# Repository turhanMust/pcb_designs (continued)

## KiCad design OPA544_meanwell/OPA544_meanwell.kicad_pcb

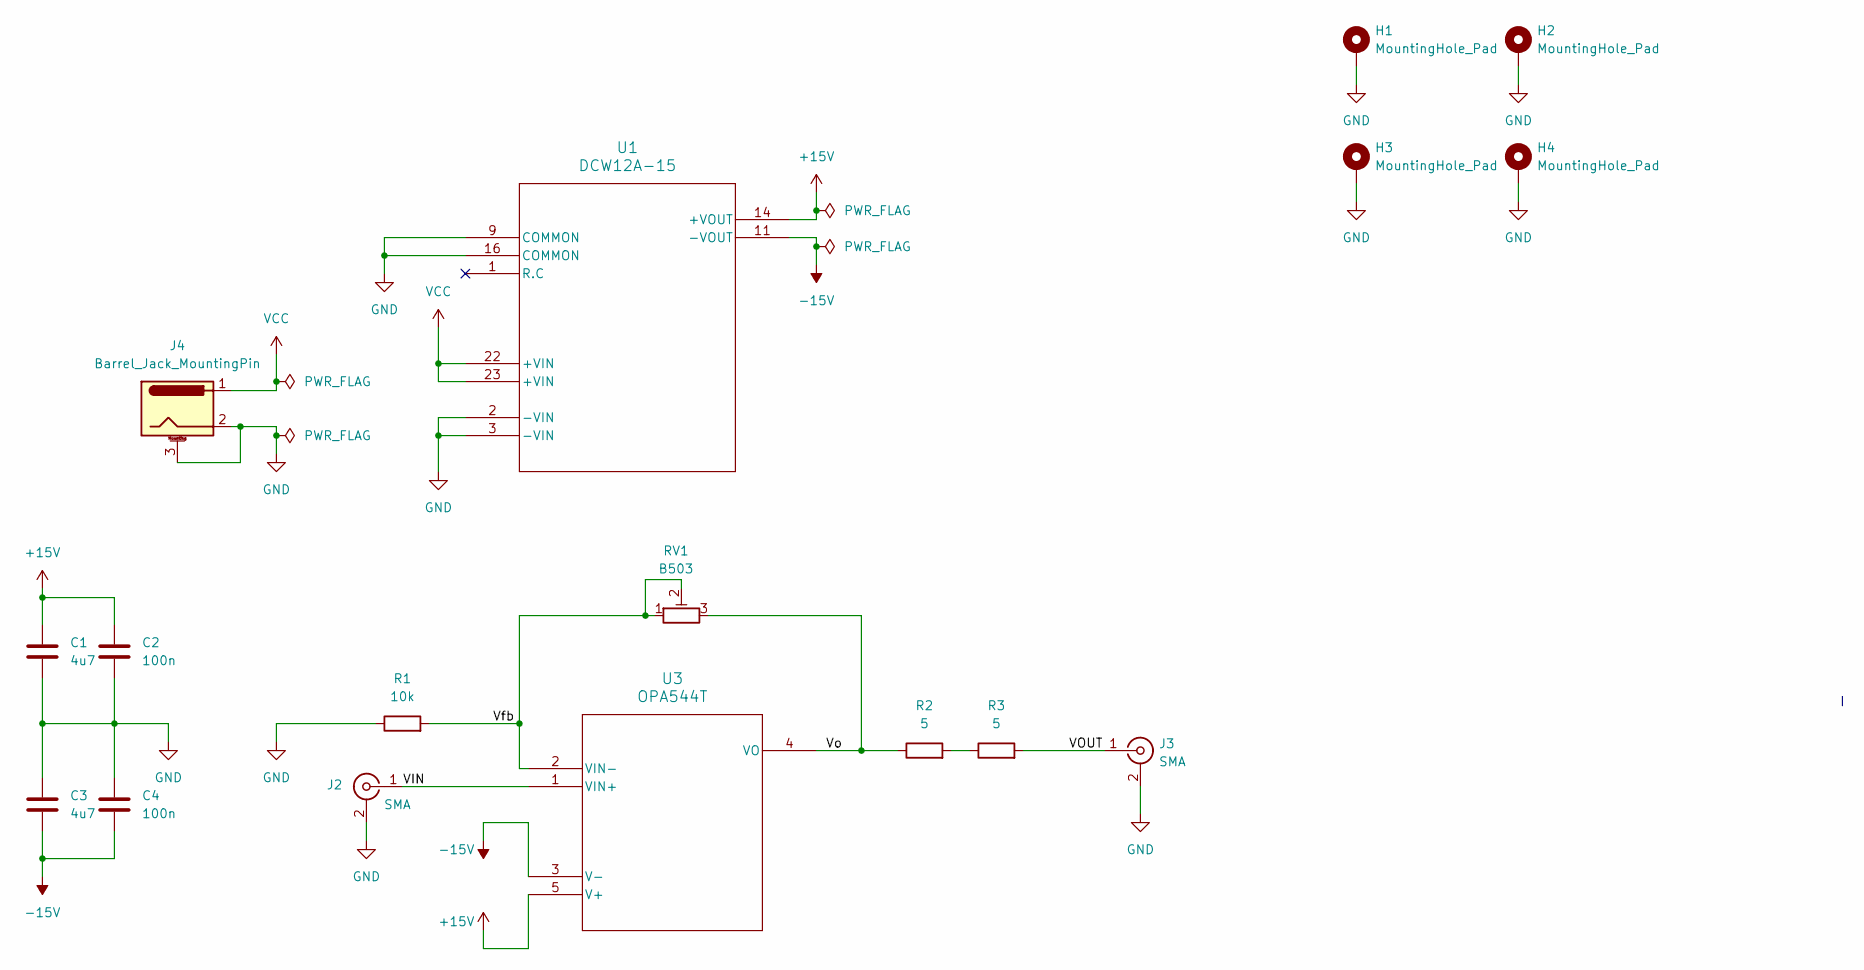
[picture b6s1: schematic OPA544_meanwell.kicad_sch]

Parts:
C1, C3: 4u7; C_0805_2012Metric
C2, C4: 100n; C_0603_1608Metric
H1, H2, H3, H4: MountingHole_Pad; MountingHole_2.5mm_Pad
J2, J3: SMA; SMA_Samtec_SMA-J-P-X-ST-EM1_EdgeMount
J4: Barrel_Jack_MountingPin; BarrelJack_Horizontal
R1: 10k; R_0603_1608Metric
R2, R3: 5; R_1210_3225Metric
RV1: B503; Potentiometer_Bourns_3296W_Vertical
U1: DCW12A-15; SCW12&slash_DCW12_MWU
U3: OPA544T; KC5

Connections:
+15V: C1.1, C2.1, U1.14 (+VOUT), U3.5 (V+)
-15V: C3.2, C4.2, U1.11 (-VOUT), U3.3 (V-)
/VIN: J2.1 (In), U3.1 (VIN+)
/VOUT: J3.1 (In), R3.2
/Vfb: R1.2, RV1.1, RV1.2, U3.2 (VIN-)
/Vo: R2.1, RV1.3, U3.4 (VO)
GND: C1.2, C2.2, C3.1, C4.1, H1.1, H2.1, H3.1, H4.1, J2.2 (Ext), J3.2 (Ext), J4.2, J4.3 (MountPin), R1.1, U1.2 (-VIN), U1.3 (-VIN), U1.9 (COMMON), U1.16 (COMMON)
unnamed: R2.2, R3.1
VCC: J4.1, U1.22 (+VIN), U1.23 (+VIN)

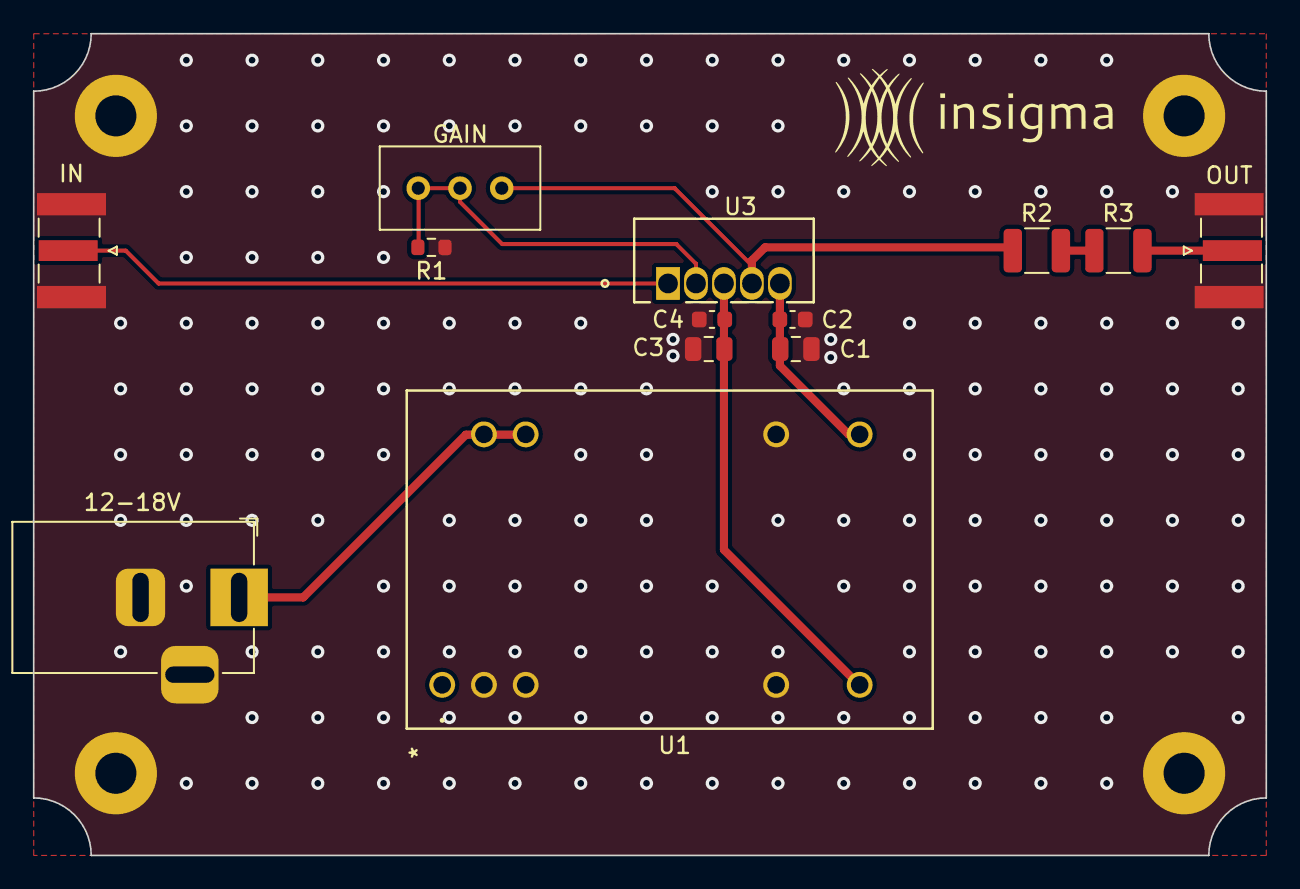
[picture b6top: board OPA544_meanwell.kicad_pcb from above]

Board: 2 copper layers, 75.0 x 50.0 mm, 17 parts (0 on the bottom side), 9 nets.

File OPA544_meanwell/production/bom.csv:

Designator,Footprint,Quantity,Value,LCSC Part #
"C1, C3",0805,2,4u7,
"C2, C4",0603,2,100n,
"J2, J3",SMA_Samtec_SMA-J-P-X-ST-EM1_EdgeMount,2,SMA,
J4,BarrelJack_Horizontal,1,Barrel_Jack_MountingPin,
R1,0603,1,10k,
"R2, R3",1210,2,5,
RV1,Potentiometer_Bourns_3296W_Vertical,1,B503,
U1,SCW12&slash_DCW12_MWU,1,DCW12A-15,
U3,KC5,1,OPA544T,

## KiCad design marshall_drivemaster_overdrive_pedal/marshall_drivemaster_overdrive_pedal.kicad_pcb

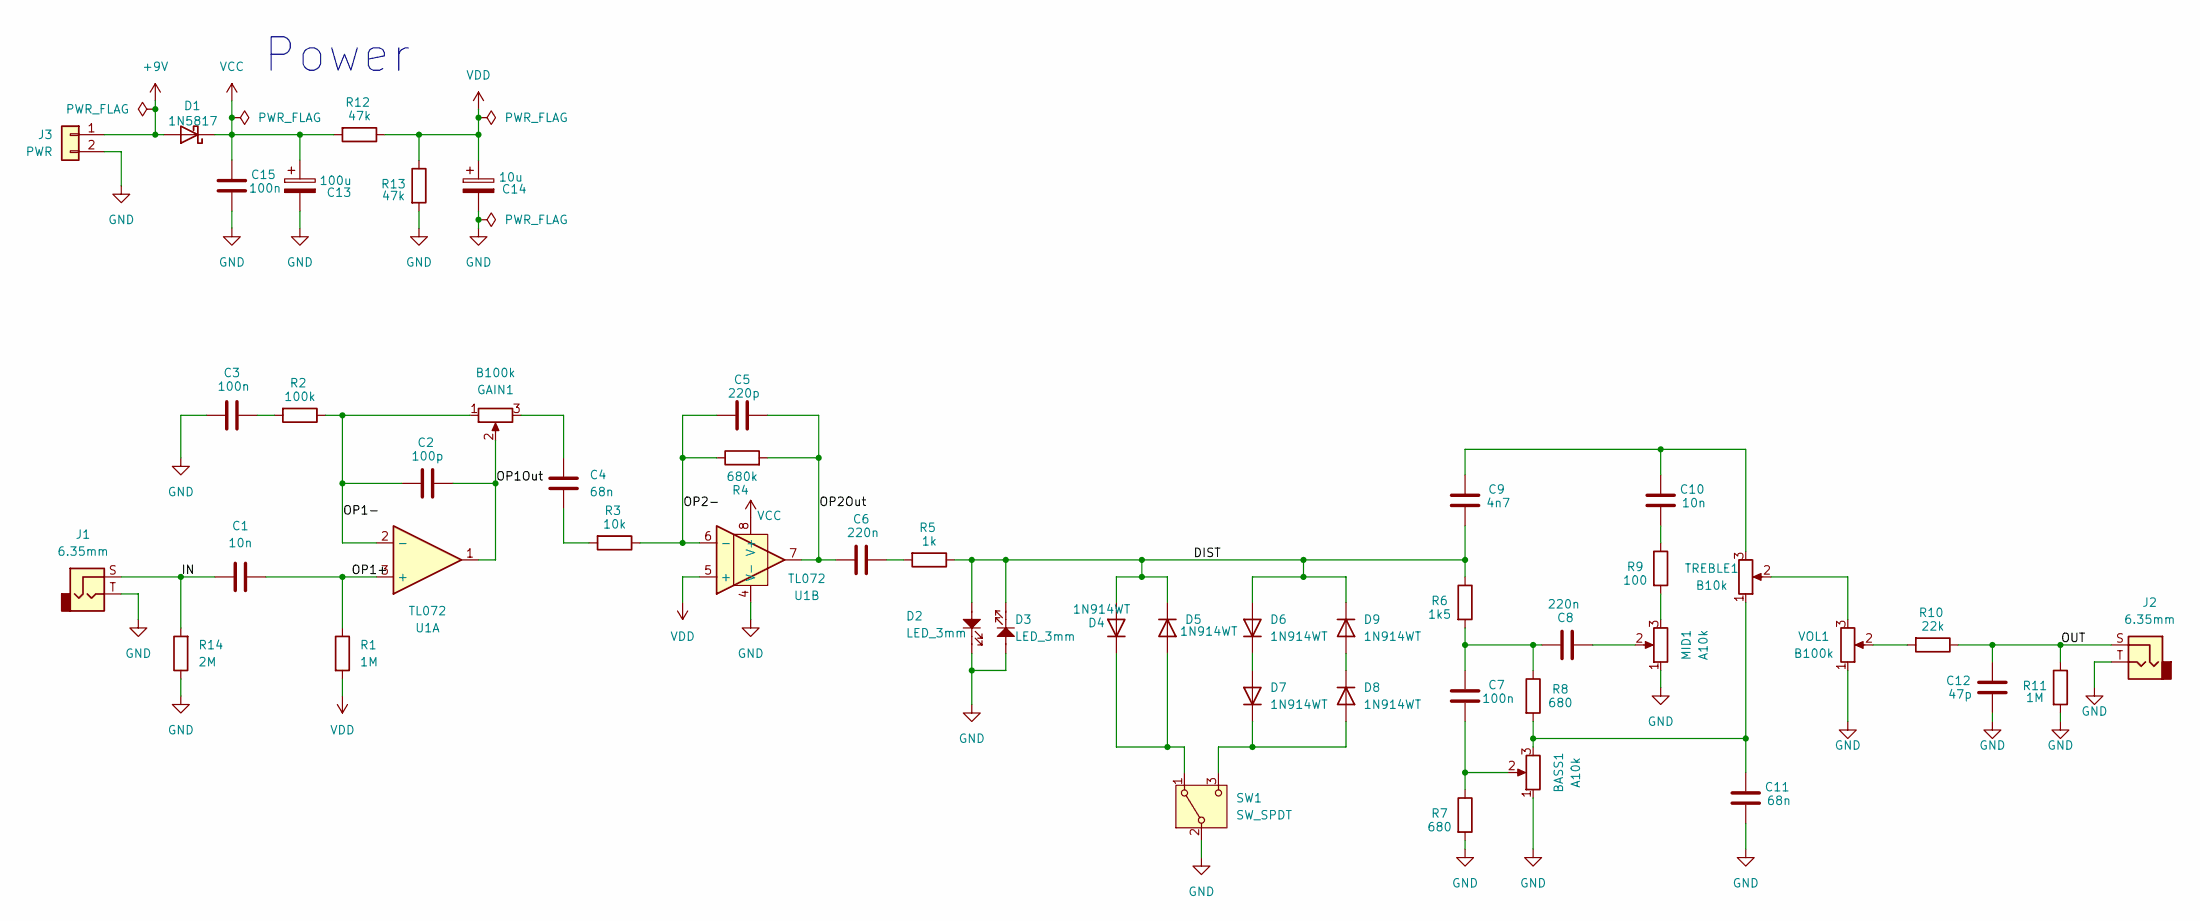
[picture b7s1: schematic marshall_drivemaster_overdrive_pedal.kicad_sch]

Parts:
BASS1: A10k; Potentiometer_Bourns_PTV09A-1_Single_Vertical
C1, C10: 10n; C_0603_1608Metric
C2: 100p; C_0603_1608Metric
C3, C7, C15: 100n; C_0603_1608Metric
C4, C11: 68n; C_0603_1608Metric
C5: 220p; C_0603_1608Metric
C6, C8: 220n; C_0603_1608Metric
C9: 4n7; C_0603_1608Metric
C12: 47p; C_0603_1608Metric
C13: 100u; CP_Radial_D5.0mm_P2.00mm
C14: 10u; CP_Radial_D5.0mm_P2.00mm
D1: 1N5817; D_DO-41_SOD81_P10.16mm_Horizontal
D2, D3: LED_3mm; LED_D3.0mm
D4, D5, D6, D7, D8, D9: 1N914WT; D_SOD-523
GAIN1: B100k; Potentiometer_Bourns_PTV09A-1_Single_Vertical
J1, J2: 6.35mm; Jack_6.35mm_Neutrik_NMJ4HCD2_Horizontal
J3: PWR; SolderWire-0.25sqmm_1x02_P4.2mm_D0.65mm_OD1.7mm
MID1: A10k; Potentiometer_Bourns_PTV09A-1_Single_Vertical
R1, R11: 1M; R_0603_1608Metric
R2: 100k; R_0603_1608Metric
R3: 10k; R_0603_1608Metric
R4: 680k; R_0603_1608Metric
R5: 1k; R_0603_1608Metric
R6: 1k5; R_0603_1608Metric
R7, R8: 680; R_0603_1608Metric
R9: 100; R_0603_1608Metric
R10: 22k; R_0603_1608Metric
R12, R13: 47k; R_0603_1608Metric
R14: 2M; R_0603_1608Metric
SW1: SW_SPDT; Switch_Toggle_SPDT_Mini_SolderLug
TREBLE1: B10k; Potentiometer_Bourns_PTV09A-1_Single_Vertical
U1: TL072; SO-8_3.9x4.9mm_P1.27mm; JLCPCB ID C90748
VOL1: B100k; Potentiometer_Bourns_PTV09A-1_Single_Vertical

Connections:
+9V: D1.2 (A), J3.1
/DIST: C9.1, D2.2, D3.1, D4.2 (A), D5.1 (K), D6.2 (A), D9.1 (K), R5.1, R6.1
/IN: C1.1, J1.S, R14.2
/OP1+: C1.2, R1.1, U1.3 (+)
/OP1-: C2.1, GAIN1.1, R2.1, U1.2 (-)
/OP1Out: C2.2, GAIN1.2, U1.1
/OP2-: C5.1, R3.1, R4.1, U1.6 (-)
/OP2Out: C5.2, C6.1, R4.2, U1.7
/OUT: C12.2, J2.S, R10.1, R11.1
GND: BASS1.1, C3.1, C11.1, C12.1, C13.2, C14.2, C15.1, D2.1, D3.2, J1.T, J2.T, J3.2, MID1.1, R7.2, R11.2, R13.2, R14.1, SW1.2 (B), U1.4 (V-), VOL1.1
unnamed: BASS1.2, C7.1, R7.1
unnamed: BASS1.3, C11.2, R8.2, TREBLE1.1
unnamed: C3.2, R2.2
unnamed: C4.1, R3.2
unnamed: C4.2, GAIN1.3
unnamed: C6.2, R5.2
unnamed: C7.2, C8.2, R6.2, R8.1
unnamed: C8.1, MID1.2
unnamed: C10.1, R9.1
unnamed: C9.2, C10.2, TREBLE1.3
unnamed: D4.1 (K), D5.2 (A), SW1.1 (A)
unnamed: D6.1 (K), D7.2 (A)
unnamed: D7.1 (K), D8.2 (A), SW1.3 (C)
unnamed: D8.1 (K), D9.2 (A)
unnamed: MID1.3, R9.2
unnamed: R10.2, VOL1.2
unnamed: TREBLE1.2, VOL1.3
VCC: C13.1, C15.2, D1.1 (K), R12.2, U1.8 (V+)
VDD: C14.1, R1.2, R12.1, R13.1, U1.5 (+)

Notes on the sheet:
Power

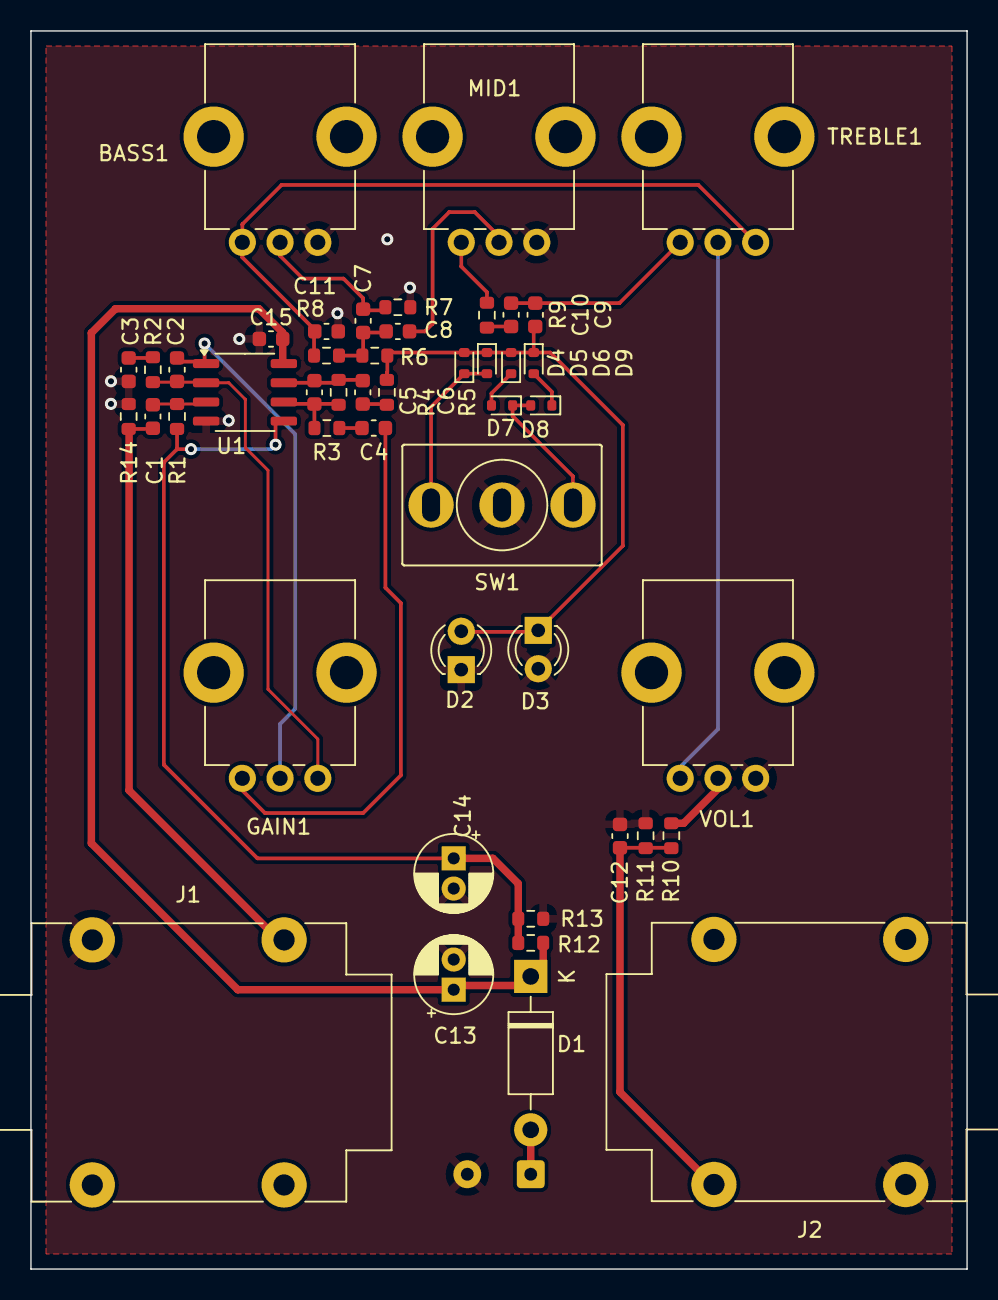
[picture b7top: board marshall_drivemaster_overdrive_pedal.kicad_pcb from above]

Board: 2 copper layers, 62.0 x 82.0 mm, 48 parts (0 on the bottom side), 29 nets.

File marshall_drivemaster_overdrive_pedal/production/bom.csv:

Designator,Footprint,Quantity,Value,LCSC Part #
"BASS1, MID1",Potentiometer_Bourns_PTV09A-1_Single_Vertical,2,A10k,
"C1, C10",0603,2,10n,
"C11, C4",0603,2,68n,
C12,0603,1,47p,
C13,CP_Radial_D5.0mm_P2.00mm,1,100u,
C14,CP_Radial_D5.0mm_P2.00mm,1,10u,
"C15, C3, C7",0603,3,100n,
C2,0603,1,100p,
C5,0603,1,220p,
"C6, C8",0603,2,220n,
C9,0603,1,4n7,
D1,D_DO-41_SOD81_P10.16mm_Horizontal,1,1N5817,
"D2, D3",LED_D3.0mm,2,LED_3mm,
"D4, D5, D6, D7, D8, D9",D_SOD-523,6,1N914WT,
"GAIN1, VOL1",Potentiometer_Bourns_PTV09A-1_Single_Vertical,2,B100k,
"J1, J2",Jack_6.35mm_Neutrik_NMJ4HCD2_Horizontal,2,6.35mm,
J3,SolderWire-0.25sqmm_1x02_P4.2mm_D0.65mm_OD1.7mm,1,PWR,
"R1, R11",0603,2,1M,
R10,0603,1,22k,
"R12, R13",0603,2,47k,
R14,0603,1,2M,
R2,0603,1,100k,
R3,0603,1,10k,
R4,0603,1,680k,
R5,0603,1,1k,
R6,0603,1,1k5,
"R7, R8",0603,2,680,
R9,0603,1,100,
SW1,Switch_Toggle_SPDT_Mini_SolderLug,1,SW_SPDT,
TREBLE1,Potentiometer_Bourns_PTV09A-1_Single_Vertical,1,B10k,
U1,SO-8_3.9x4.9mm_P1.27mm,1,TL072,

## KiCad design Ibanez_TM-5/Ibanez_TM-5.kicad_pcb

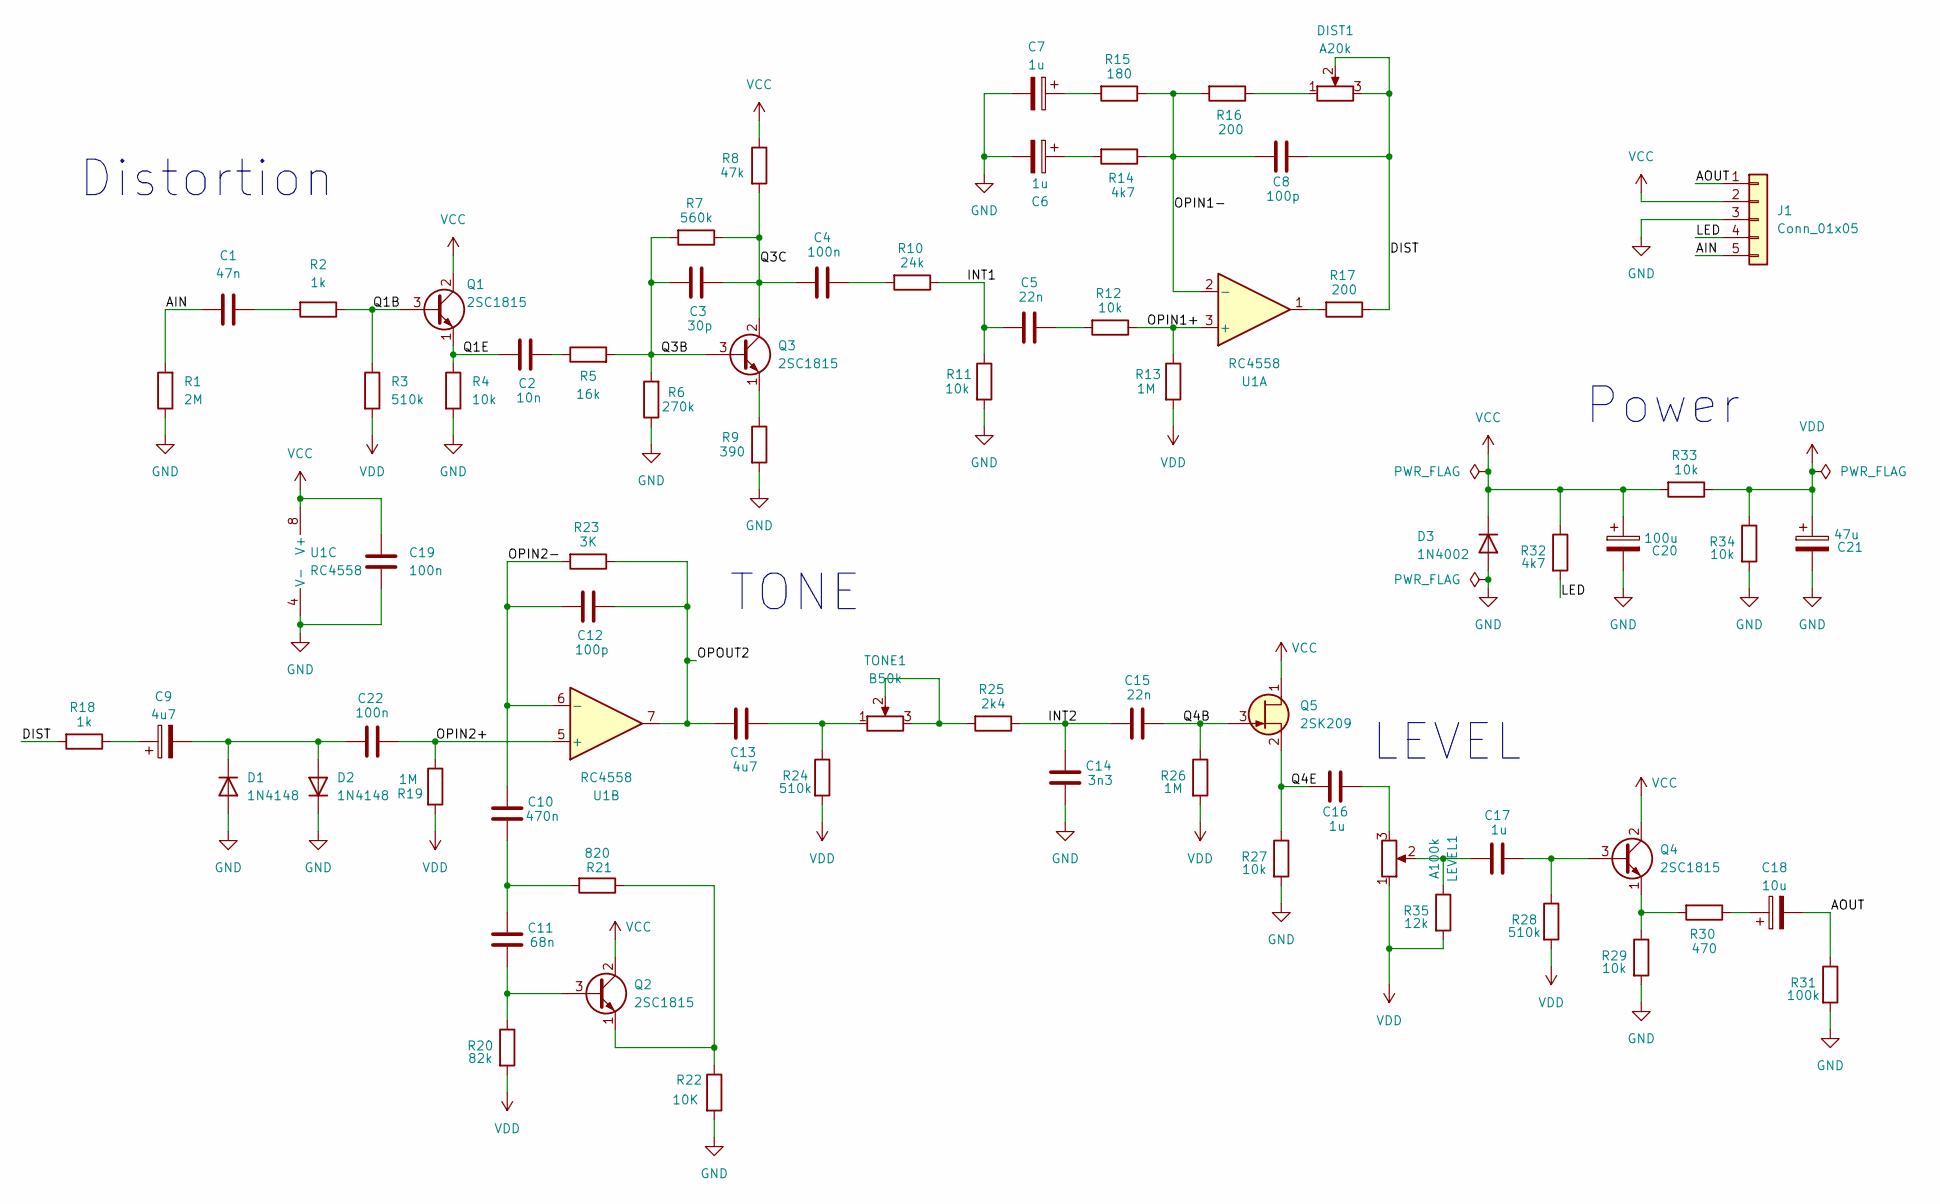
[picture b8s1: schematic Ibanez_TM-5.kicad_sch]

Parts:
C1: 47n; C_0603_1608Metric
C2: 10n; C_0603_1608Metric
C3: 30p; C_0603_1608Metric
C4, C19, C22: 100n; C_0603_1608Metric
C5, C15: 22n; C_0603_1608Metric
C6, C7: 1u; CP_Elec_4x5.3
C8, C12: 100p; C_0603_1608Metric
C9: 4u7; CP_Elec_4x5.4
C10: 470n; C_0603_1608Metric
C11: 68n; C_0603_1608Metric
C13: 4u7; C_0603_1608Metric
C14: 3n3; C_0603_1608Metric
C16, C17: 1u; C_0603_1608Metric
C18: 10u; CP_Elec_5x5.3
C20: 100u; CP_Radial_D5.0mm_P2.00mm
C21: 47u; CP_Elec_5x5.3
D1, D2: 1N4148; D_DO-35_SOD27_P7.62mm_Horizontal
D3: 1N4002; D_DO-41_SOD81_P10.16mm_Horizontal
DIST1: A20k; Potentiometer_Bourns_PTV09A-1_Single_Vertical
J1: Conn_01x05; SolderWire-0.5sqmm_1x05_P4.6mm_D0.9mm_OD2.1mm
LEVEL1: A100k; Potentiometer_Bourns_PTV09A-1_Single_Vertical
Q1, Q2, Q3, Q4: 2SC1815; TO-92L_Inline
Q5: 2SK209; SC-59
R1: 2M; R_0603_1608Metric
R2, R18: 1k; R_0603_1608Metric
R3, R24, R28: 510k; R_0603_1608Metric
R4, R11, R12, R27, R29, R33, R34: 10k; R_0603_1608Metric
R5: 16k; R_0603_1608Metric
R6: 270k; R_0603_1608Metric
R7: 560k; R_0603_1608Metric
R8: 47k; R_0603_1608Metric
R9: 390; R_0603_1608Metric
R10: 24k; R_0603_1608Metric
R13, R19, R26: 1M; R_0603_1608Metric
R14, R32: 4k7; R_0603_1608Metric
R15: 180; R_0603_1608Metric
R16, R17: 200; R_0603_1608Metric
R20: 82k; R_0603_1608Metric
R21: 820; R_0603_1608Metric
R22: 10K; R_0603_1608Metric
R23: 3K; R_0603_1608Metric
R25: 2k4; R_0603_1608Metric
R30: 470; R_0603_1608Metric
R31: 100k; R_0603_1608Metric
R35: 12k; R_0603_1608Metric
TONE1: B50k; TRIM_PT01-D125D-B503
U1: RC4558; SOIC-8_3.9x4.9mm_P1.27mm

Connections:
/AIN: C1.1, J1.5, R1.2
/AOUT: C18.2, J1.1, R31.1
/DIST: C8.2, DIST1.2, DIST1.3, R17.1, R18.2
/INT1: C5.1, R10.1, R11.1
/INT2: C14.2, C15.1, R25.1
/LED: J1.4, R32.2
/OPIN1+: R12.1, R13.1, U1.3 (+)
/OPIN1-: C8.1, R14.1, R15.1, R16.2, U1.2 (-)
/OPIN2+: C22.2, R19.1, U1.5 (+)
/OPIN2-: C10.2, C12.1, R23.2, U1.6 (-)
/OPOUT2: C12.2, C13.1, R23.1, U1.7
/Q1B: Q1.3 (B), R2.1, R3.1
/Q1E: C2.1, Q1.1 (E), R4.1
/Q3B: C3.1, Q3.3 (B), R5.2, R6.2, R7.2
/Q3C: C3.2, C4.1, Q3.2 (C), R7.1, R8.2
/Q4B: C15.2, Q5.3 (G), R26.1
/Q4E: C16.1, Q5.2 (S), R27.1
GND: C6.2, C7.2, C14.1, C19.1, C20.2, C21.2, D1.2 (A), D2.1 (K), D3.2 (A), J1.3, R1.1, R4.2, R6.1, R9.2, R11.2, R22.2, R27.2, R29.2, R31.2, R34.2, U1.4 (V-)
unnamed: C1.2, R2.2
unnamed: C2.2, R5.1
unnamed: C4.2, R10.2
unnamed: C5.2, R12.2
unnamed: C6.1, R14.2
unnamed: C7.1, R15.2
unnamed: C9.1, R18.1
unnamed: C10.1, C11.2, R21.2
unnamed 26: C13.2, R24.1, TONE1.1; also elsewhere on the board
unnamed 27: C16.2, LEVEL1.3; also elsewhere on the board
unnamed 28: C17.1, LEVEL1.2, R35.1; also elsewhere on the board
unnamed: C18.1, R30.1
unnamed: C9.2, C22.1, D1.1 (K), D2.2 (A)
unnamed: DIST1.1, R16.1
unnamed: C11.1, Q2.3 (B), R20.1
unnamed: Q2.1 (E), R21.1, R22.1
unnamed: Q3.1 (E), R9.1
unnamed: C17.2, Q4.3 (B), R28.1
unnamed: Q4.1 (E), R29.1, R30.2
unnamed: R17.2, U1.1
unnamed 38: R25.2, TONE1.2, TONE1.3; also elsewhere on the board
VCC: C19.2, C20.1, D3.1 (K), J1.2, Q1.2 (C), Q2.2 (C), Q4.2 (C), Q5.1 (D), R8.1, R32.1, R33.2, U1.8 (V+)
VDD: C21.1, LEVEL1.1, R3.2, R13.2, R19.2, R20.2, R24.2, R26.2, R28.2, R33.1, R34.1, R35.2; also elsewhere on the board

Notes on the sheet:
Distortion
LEVEL
Power
TONE

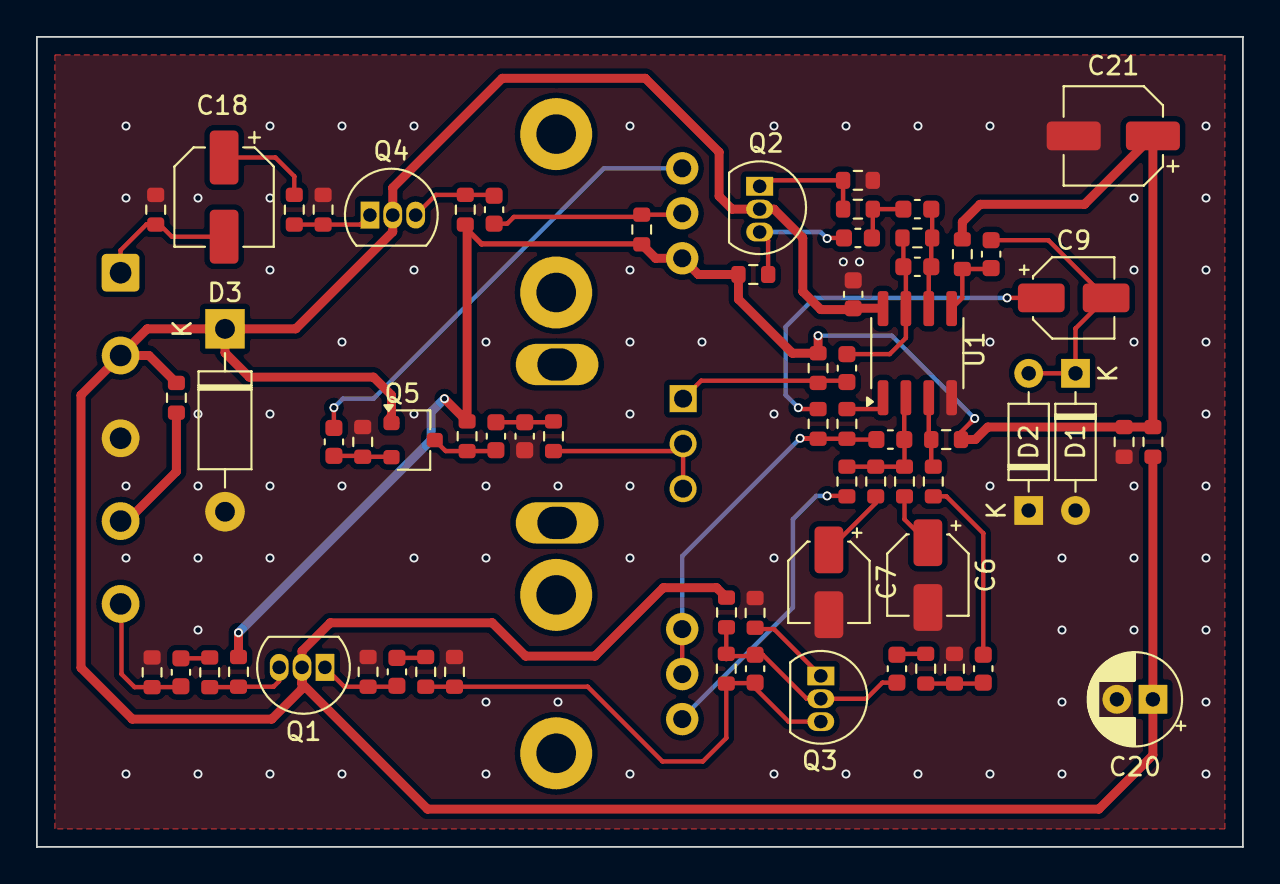
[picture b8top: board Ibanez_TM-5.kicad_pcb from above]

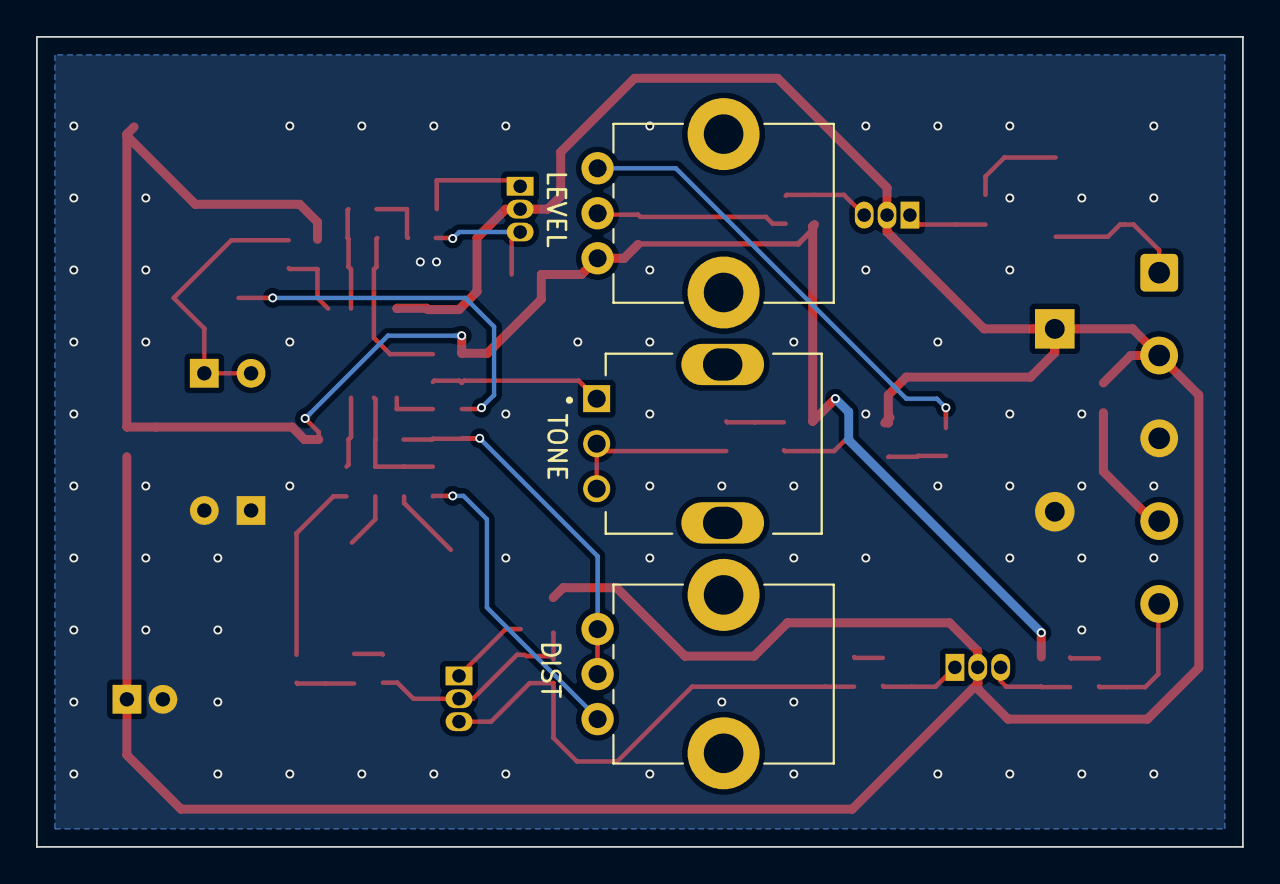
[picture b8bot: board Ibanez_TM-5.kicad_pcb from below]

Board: 2 copper layers, 67.0 x 45.0 mm, 70 parts (3 on the bottom side), 41 nets.

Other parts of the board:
LEVEL: A100k; Potentiometer_Bourns_PTV09A-1_Single_Vertical
TONE: B50k; TRIM_PT01-D125D-B503

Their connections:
unnamed 26: TONE.1; also elsewhere on the board
unnamed 27: LEVEL.3; also elsewhere on the board
unnamed 28: LEVEL.2; also elsewhere on the board
unnamed 38: TONE.2, TONE.3; also elsewhere on the board
VDD: LEVEL.1; also elsewhere on the board

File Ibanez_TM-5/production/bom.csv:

Designator,Footprint,Quantity,Value,LCSC Part #
C1,0603,1,47n,
C10,0603,1,470n,
C11,0603,1,68n,
"C12, C8",0603,2,100P,
C13,0603,1,4u7,
C14,0603,1,3n3,
"C15, C5",0603,2,22n,
"C16, C17",0603,2,1u,
C18,CP_Radial_D5.0mm_P2.00mm,1,10u,
"C19, C22, C4",0603,3,100n,
C2,0603,1,10n,
C20,CP_Radial_D5.0mm_P2.00mm,1,100u,
C21,CP_Radial_D5.0mm_P2.00mm,1,47u,
C3,0603,1,30p,
"C6, C7",CP_Radial_D5.0mm_P2.00mm,2,1u,
C9,CP_Radial_D5.0mm_P2.00mm,1,4u7,
"D1, D2",D_DO-35_SOD27_P7.62mm_Horizontal,2,1N4148,
D3,D_DO-41_SOD81_P10.16mm_Horizontal,1,1N4002,
DIST1,Potentiometer_Bourns_PTV09A-1_Single_Vertical,1,A20k,
J1,SolderWire-0.5sqmm_1x05_P4.6mm_D0.9mm_OD2.1mm,1,Conn_01x05,
LEVEL1,Potentiometer_Bourns_PTV09A-1_Single_Vertical,1,A100k,
"Q1, Q2, Q3, Q5",TO-92_Inline,4,2SC1815,
Q4,TO-92,1,2N3819,
R1,0603,1,2M,
R10,0603,1,24k,
"R11, R12, R22, R27, R29, R33, R34, R4",0603,8,10k,
"R13, R19, R26",0603,3,1M,
"R14, R32",0603,2,4k7,
R15,0603,1,180,
"R16, R17",0603,2,200,
"R18, R2",0603,2,1k,
R20,0603,1,82k,
R21,0603,1,820,
R23,0603,1,3K,
"R24, R28, R3",0603,3,510k,
R25,0603,1,2k4,
R30,0603,1,470,
R31,0603,1,100k,
R35,0603,1,12k,
R5,0603,1,16k,
R6,0603,1,270k,
R7,0603,1,560k,
R8,0603,1,47k,
R9,0603,1,390,
TONE1,TRIM_PT01-D125D-B503,1,B50k,
U1,SOIC-8_3.9x4.9mm_P1.27mm,1,RC4558,
